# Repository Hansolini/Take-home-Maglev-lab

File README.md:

# Take-home Maglev lab \:magnet\:

<table align="center">
  <tr>
    <td align="center">
      <br>
      1) Current version of the hardware.
    </td>
    <td align="center">
      <br>
      2) Overview of the current PCB.
    </td>
    <td align="center">
      <br>
      2) Magnetic structure of the system.
    </td>
  </tr>
</table>

The "Take-home Maglev lab" is a small lab in development at the Norwegian University of Science and Technology (NTNU), University of Padova, Italy, and University in Stavanger, Norway. The setup is tailored to help students learn control and related fields, and is intended as a kit that students can bring home and assemble independently, with additional lab assignments for teaching anything from fundamental to advanced concepts within control engineering.

If you want to see how the platform looks like and how effective it is to achieve levitation (actually with a PD controller in this case), see [this](https://youtube.com/shorts/XnbO15yq0vE) and [this](https://youtube.com/shorts/F0SiuVEP2tM) videos.

As for this repository, it contains a
- **[MATLAB simulator](./simulation),** implementing several models with examples. See [main.mlx](./simulation/main.mlx) for a guide on how to use it.
- **[Design files & software](./physical_system),** and thus PCB files, test code, with examples for how to use the physical system.
- **[Student contributions](./student_contributions),** i.e., theses and project reports from the students that have contributed to the project.

The following is a table about such student reports, summarizing also the hardware development history.
## Project reports \:books\:
### 2022
 1. [M. Brønstad, J. O. Deila, J. Dyerskog, and M. Langklopp, "Magnetic levitation system: Design, prototyping and testing of a digital PID-controller", B.S. thesis, ITK, NTNU, Trondheim, 2022.](./student_contributions/literature/2022_NTNU_bachelor_thesis_MJJM.pdf)
 2. [A. Morselli, "Re-design of a magnetic levitation platform: from an early prototype to a working system", B.S. thesis, DDD, UNIPD, Padova, 2022.](./student_contributions/literature/2022_UNIPD_bachelor_thesis_alberto_morselli.pdf)
 3. [A. Nicetto, "State Space Observers and Controllers for a Take-Home Magnetic Levitation System", B.S. thesis, DDD, UNIPD, Padova, 2022.](./student_contributions/literature/2022_UNIPD_bachelor_thesis_andrea_nicetto.pdf)
 4. [F. D. Marchi, "Modeling and Control of a Magnetic Levitation System", B.S. thesis, DDD, UNIPD, Padova, 2022.](./student_contributions/literature/2022_UNIPD_bachelor_thesis_francesco_de_marchi.pdf)
### 2023
1. [H. A. Engmark, K. T. Hoang, "Modeling and Control of a Magnetic Levitation Platform.", presented at the 22nd IFAC World Congress, Yokohama, 2023 pp. 7276-7281. ](./media/literature/maglev_model_description.pdf)
2. [A. Lincetto, "Towards a Pythonic framework for control and analysis of magnetic levitation systems", B.S. thesis, DDD, UNIPD, Padova, 2023.](./student_contributions/literature/2023_UNIPD_bachelor_thesis_alessandro_lincetto.pdf)
3. [G. Piccolin, "considerations on the software and hardware requirements for the implementation of take-home Maglev control labs", B.S. thesis, DDD, UNIPD, Padova, 2023.](./student_contributions/literature/2023_UNIPD_bachelor_thesis_giulio_piccolin.pdf)
4. [S. Graffer, "State estimation of a Maglev system with the Luenberger observer", Project thesis, ITK, NTNU, Trondheim, 2023.](./student_contributions/literature/2023_NTNU_project_thesis_sverre_graffer.pdf)
5. [P. I. D. K. Fosmo, "Control of a magnetic levitation system using feedback linearization", Project thesis, ITK, NTNU, Trondheim, 2023.](./student_contributions/literature/2023_NTNU_project_thesis_pål_fosmo.pdf)
6. [S. A. Senkaya, "A take home portable MagLev lab for learning electronics and control", Project thesis, ITK, NTNU, Trondheim, 2023.](./student_contributions/literature/2023_NTNU_project_thesis_sacit_ali_senkaya.pdf)
### 2024
1. [P. I. D. K. Fosmo, S. A. Senkaya, S. Graffer, H. A. Engmark, D. Varagnolo, "Maggy: Hands-on control learning with a maglev system", M.S. thesis, ITK, NTNU, Trondheim, 2024.](https://ntnuopen.ntnu.no/ntnu-xmlui/handle/11250/3153592)
2. [P. I. D. K. Fosmo, H. A. Engmark, D. Varagnolo, "Maglev Systems for Control Education", Maglev24, Malmö, 2024.](https://bth.diva-portal.org/smash/get/diva2:1918096/FULLTEXT01.pdf)
3. [A. Dal Bello, "Tracking Visual Markers For Maglev Platforms", B.S. thesis, DSMN, UNIVE, Venezia, 2024.](./student_contributions/literature/2024_UNIVE_bachelor_thesis_alessandra_dal_bello.pdf)
4. [G. D'Auria, "Computer based state observers for magnet systems", B.S. thesis, DEI, UNIPD, Padova, 2024.](./student_contributions/literature/2024_UNIPD_bachelor_thesis_giuseppe_d'auria.pdf)
### 2025
1. [Ø. Damsgaard, "Moving horizon state estimation for predictive control of magnetic levitation systems", M.S. thesis, ITK, NTNU, Trondheim, 2025](./student_contributions/literature/2025_MSc_thesis_-_Ørnulf_Damsgaard_-_Moving_horizon_state_estimation_for_predictive_control_of_magnetic_levitation_systems.pdf.pdf)
2. [M. Mjelde, "Robust Model Predictive Control for a Magnetic Levitation System", M.S. thesis, ITK, NTNU, Trondheim, 2025](./student_contributions/literature/2025_MSc_thesis_-_Mikael_Mjelde_-_Robust_Model_Predictive_Control_for_a_Maglev.pdf)
3. [L. Ongaro, "Adapting a maglev system for the ball and beam control", B.S. thesis, University of Padova, 2025](./student_contributions/literature/2025_BSc_thesis_Ongaro_Leonardo_Adapting_a_maglev_system_for_the_ball_and_beam_control.pdf)
4. [M. Palamin, "Comunicazione tra un sistema maglev e dispositivi esterni: implementazione e implicazioni per la didattica sulla Teoria del Controllo", B.S. thesis, University of Padova, 2025](./student_contributions/literature/2025_BSc_thesis_Palamin_Manuel_Comunicazione_tra_un_sistema_maglev_e_dispositivi_esterni.pdf)
5. [T. Chinello, "Bode and Nyquist plots for the analysis and control of a magnetic levitation system", B.S. thesis, University of Padova, 2025](./student_contributions/literature/2025_BSc_thesis_Chinello_Tommaso_Bode_and_Nyquist_plots_for_the_analysis_and_control_of_a_magnetic_levitation_system.pdf)
6. [T. A. Jonsson, "Implementation of a Moving Horizon Estimator Using the Acados Framework", M.S. project, ITK, NTNU, Trondheim, 2025](./student_contributions/literature/2025_Prosjektoppgave_-_Thomas_Aleksander_Jonsson_-_MHE_for_Maggy.pdf)
7. [E. Bruaset, "Acados-based Implementation of Nonlinear MPC for Magnetic Levitation", M.S. project, ITK, NTNU, Trondheim, 2025](./student_contributions/literature/2025_Prosjektoppgave_-_Eivind_Bruaset_-_Acados_for_Maggy.pdf)
8. [L. Edvardsen, "Reinforcement Learning for MagLev Control", M.S. project, ITK, NTNU, Trondheim, 2025](./student_contributions/literature/2025_Prosjektoppgave_-_Linus_Edvardsen_-_RL_for_Maggy.pdf)
9. [M. Jullum Faanes, "CasADi-based Implementation of Nonlinear MPC for Magnetic Levitation", M.S. project, ITK, NTNU, Trondheim, 2025](./student_contributions/literature/2025_Prosjektoppgave_-_Marius_Jullum_Faanes_-_SMPC_for_Maggy.pdf)

## Development history \:rocket\:
| **Version** | **Developer**                                                  | **Goal**                                                      | **Development period** |      **Status**      | **Result**                  |
| ----------- | -------------------------------------------------------------- | ------------------------------------------------------------- | ---------------------- | :------------------: | --------------------------- |
| V1.0        | M. Brønstad <br> J. O. Deila <br> J. Dyrskog <br> M. Langklopp | Levitaion                                                     | Spring 2022            | \:white_check_mark\: | Stable levitation ~ 2 min   |
| V2.0        | M. Brønstad <br> J. O. Deila <br> J. Dyrskog                   | Smaller form factor, more robust                              | Summer 2022            | \:white_check_mark\: | Stable levitation >> 2 min  |
| V2.5        | JH Technical AS                                                | Fix minor bugs, improve heating and components                | Spring 2024            | \:white_check_mark\: | Stable levitation >> 2 min  |
| V2.6        | A. Morselli                                                    | Fix faulty wiring, changing sensors                           | Spring 2024            | \:white_check_mark\: | Stable levitation >> 30 min |
| V2.7        | A. Morselli                                                    | Modular design and testbench for V3.0                         | Spring 2024            | \:white_check_mark\: | Decisions on design         |
| V3.0        | A. Morselli                                                    | Modular redesign for first 'Take-home lab'                    | Summer 2024            | \:white_check_mark\: | Decisions on design         |
| V3.1        | M. Leroux                                                      | Adding USB-C power                                            | Fall 2024              | \:white_check_mark\: | Improved power delivery     |
| V4.0        | M. Leroux                                                      | New form factor and additional sensing for improved stability | Fall 2024              | \:white_check_mark\: | Improved control            |
| V4.1        | R. Antonello                                                   | Rerouting PCB tracks and updating components                  | Spring 2025            | \:white_check_mark\: | Meets IPC standards         |
| V4.2        | K. Blom                                                        | Creating a MISO version of the board                          | Spring 2025            | \:white_check_mark\: | MISO board                  |
| V4.3        | A. Morselli                                                    | Improving EM compatibility via some rerouting                 | Fall 2025              | \:white_check_mark\: | Improved EM compatibility   |

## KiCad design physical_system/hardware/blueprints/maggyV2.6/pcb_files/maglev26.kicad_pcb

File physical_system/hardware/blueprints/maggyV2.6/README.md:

#### About the protective covers
All the components are placed slightly off-center with the outline of the PCB. The protective covers are similarly misaligned so that they align well with the PCB.

The cover with the hole is the bottom plate, with the hole giving access to the reset button on the Teensy 4.1.

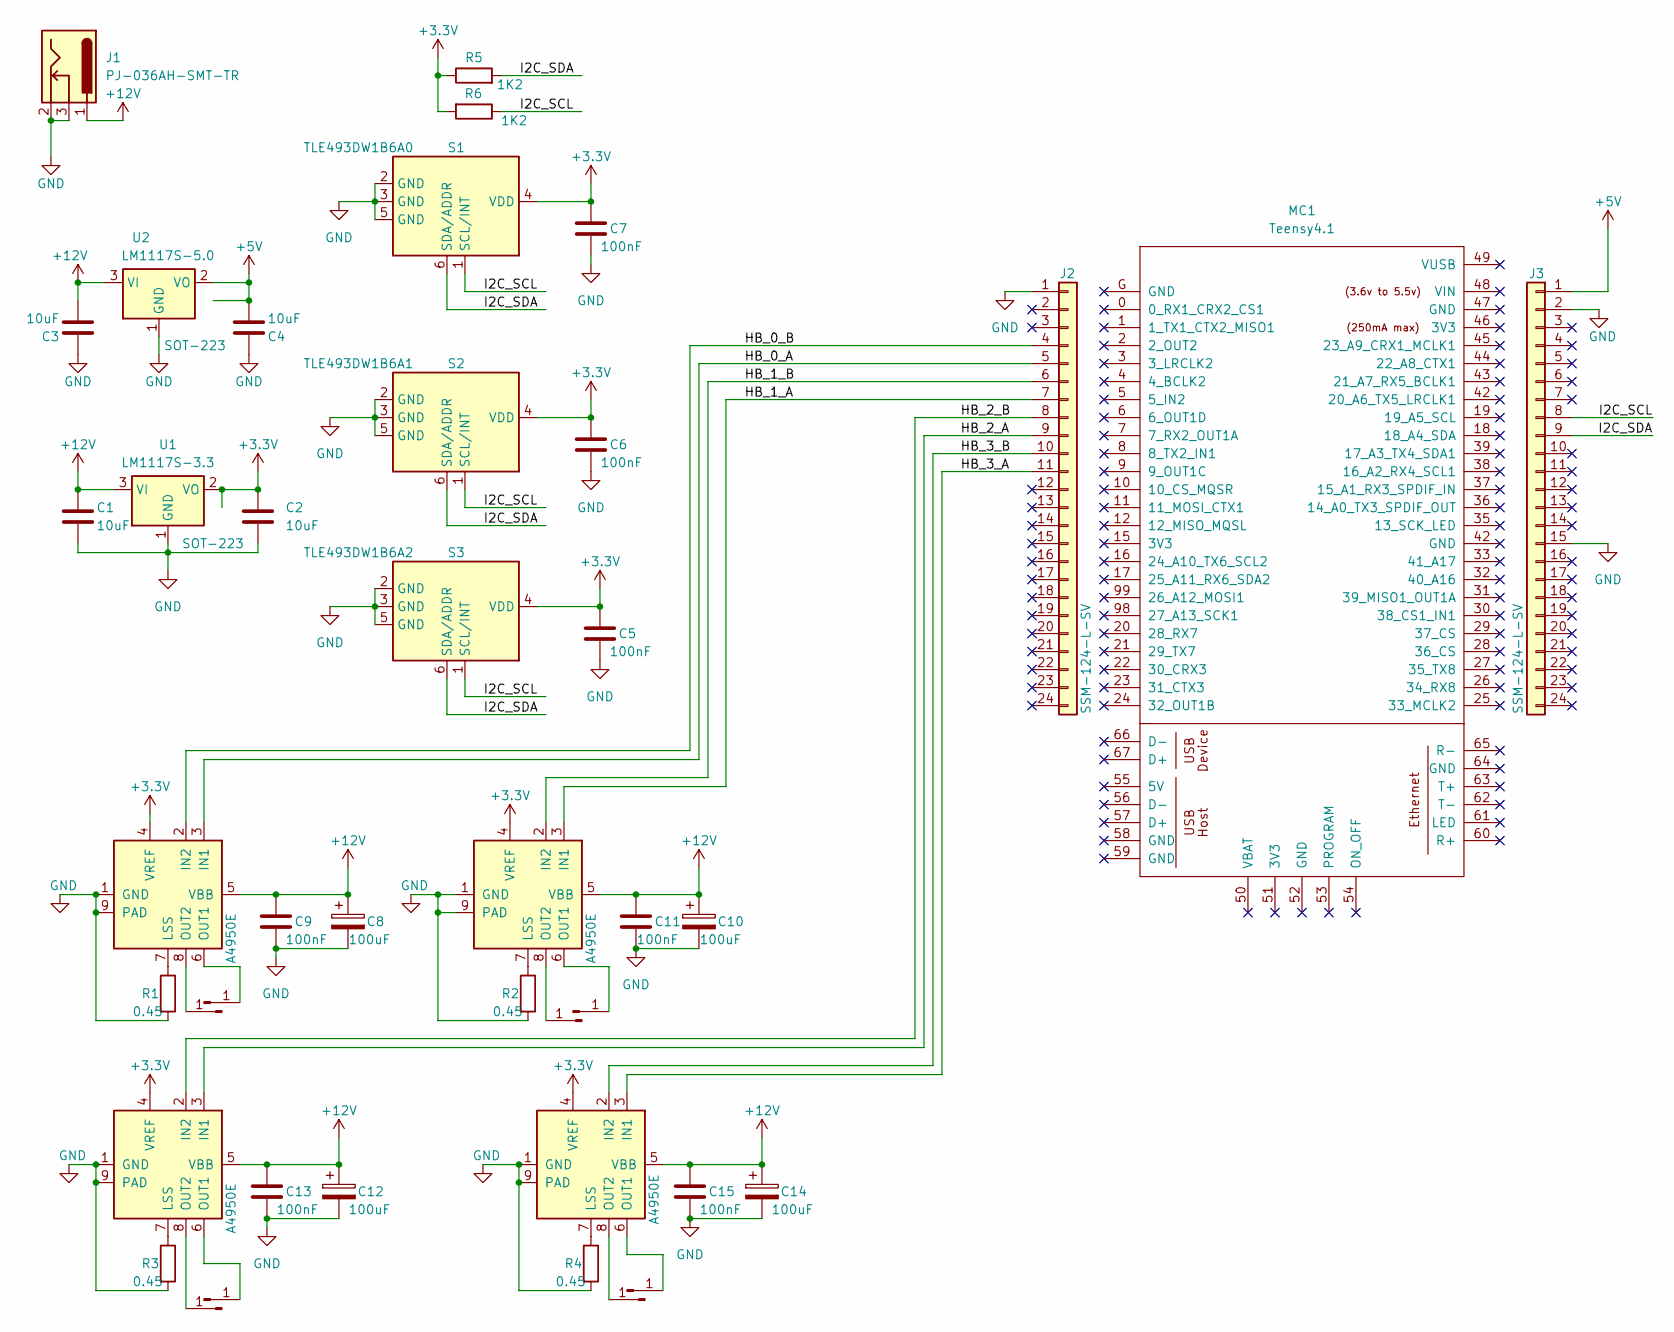
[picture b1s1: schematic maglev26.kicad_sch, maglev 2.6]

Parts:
1_1, 1_2, 2_1, 2_2, 3_1, 3_2, 4_1, 4_2: solenoid; TestPoint_Pad_1.5x1.5mm
C1, C2, C3, C4: 10uF; C_0805_2012Metric
C5, C6, C7, C9, C11, C13, C15: 100nF; C_0603_1608Metric
C8, C10, C12, C14: 100uF; CP_Elec_6.3x7.7
J1: PJ-036AH-SMT-TR; BarrelJack_CUI_PJ-036AH-SMT_Horizontal
J2, J3: SSM-124-L-SV; PinSocket_1x24_P2.54mm_Vertical_SMD_Pin1Left
M1, M2, M3, M4: A4950E; SOIC-8-1EP_3.9x4.9mm_P1.27mm_EP2.41x3.3mm
MC1: Teensy4.1; teensy 4.1
R1, R2, R3, R4: 0.45; R_1206_3216Metric_Pad1.30x1.75mm_HandSolder
R5, R6: 1K2; R_0805_2012Metric
S1: TLE493DW1B6A0; SOT-23-6
S2: TLE493DW1B6A1; SOT-23-6
S3: TLE493DW1B6A2; SOT-23-6
U1: LM1117S-3.3; SOT-223-3_TabPin2
U2: LM1117S-5.0; SOT-223-3_TabPin2

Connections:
+3.3V: C2.1, C5.2, C6.2, C7.2, M1.4 (VREF), M2.4 (VREF), M3.4 (VREF), M4.4 (VREF), R5.1, R6.2, S1.4 (VDD), S2.4 (VDD), S3.4 (VDD), U1.2 (VO); also elsewhere on the board
+5V: C4.2, J3.1, U2.2 (VO); also elsewhere on the board
+12V: C1.1, C3.2, C8.1, C9.1, C10.1, C11.1, C12.1, C13.1, C14.1, C15.1, J1.1, M1.5 (VBB), M2.5 (VBB), M3.5 (VBB), M4.5 (VBB), U1.3 (VI), U2.3 (VI); also elsewhere on the board
/HB_0_A: J2.5, M1.3 (IN1)
/HB_0_B: J2.4, M1.2 (IN2)
/HB_1_A: J2.7, M2.3 (IN1)
/HB_1_B: J2.6, M2.2 (IN2)
/HB_2_A: J2.9, M3.3 (IN1)
/HB_2_B: J2.8, M3.2 (IN2)
/HB_3_A: J2.11, M4.3 (IN1)
/HB_3_B: J2.10, M4.2 (IN2)
/I2C_SCL: J3.8, R6.1, S1.1 (SCL/INT), S2.1 (SCL/INT), S3.1 (SCL/INT)
/I2C_SDA: J3.9, R5.2, S1.6 (SDA/ADDR), S2.6 (SDA/ADDR), S3.6 (SDA/ADDR)
GND: C1.2, C2.2, C3.1, C4.1, C5.1, C6.1, C7.1, C8.2, C9.2, C10.2, C11.2, C12.2, C13.2, C14.2, C15.2, J1.2, J1.3, J2.1, J3.2, J3.15, M1.1 (GND), M1.9 (PAD), M2.1 (GND), M2.9 (PAD), M3.1 (GND), M3.9 (PAD), M4.1 (GND), M4.9 (PAD), R1.2, R2.2, R3.2, R4.2, S1.2 (GND), S1.3 (GND), S1.5 (GND), S2.2 (GND), S2.3 (GND), S2.5 (GND), S3.2 (GND), S3.3 (GND), S3.5 (GND), U1.1 (GND), U2.1 (GND); also elsewhere on the board
unnamed: 1_1.1, M1.6 (OUT1)
unnamed: 1_2.1, M1.8 (OUT2)
unnamed: 2_1.1, M2.6 (OUT1)
unnamed: 2_2.1, M2.8 (OUT2)
unnamed: 3_1.1, M3.6 (OUT1)
unnamed: 3_2.1, M3.8 (OUT2)
unnamed: 4_1.1, M4.6 (OUT1)
unnamed: 4_2.1, M4.8 (OUT2)
unnamed: M1.7 (LSS), R1.1
unnamed: M2.7 (LSS), R2.1
unnamed: M3.7 (LSS), R3.1
unnamed: M4.7 (LSS), R4.1

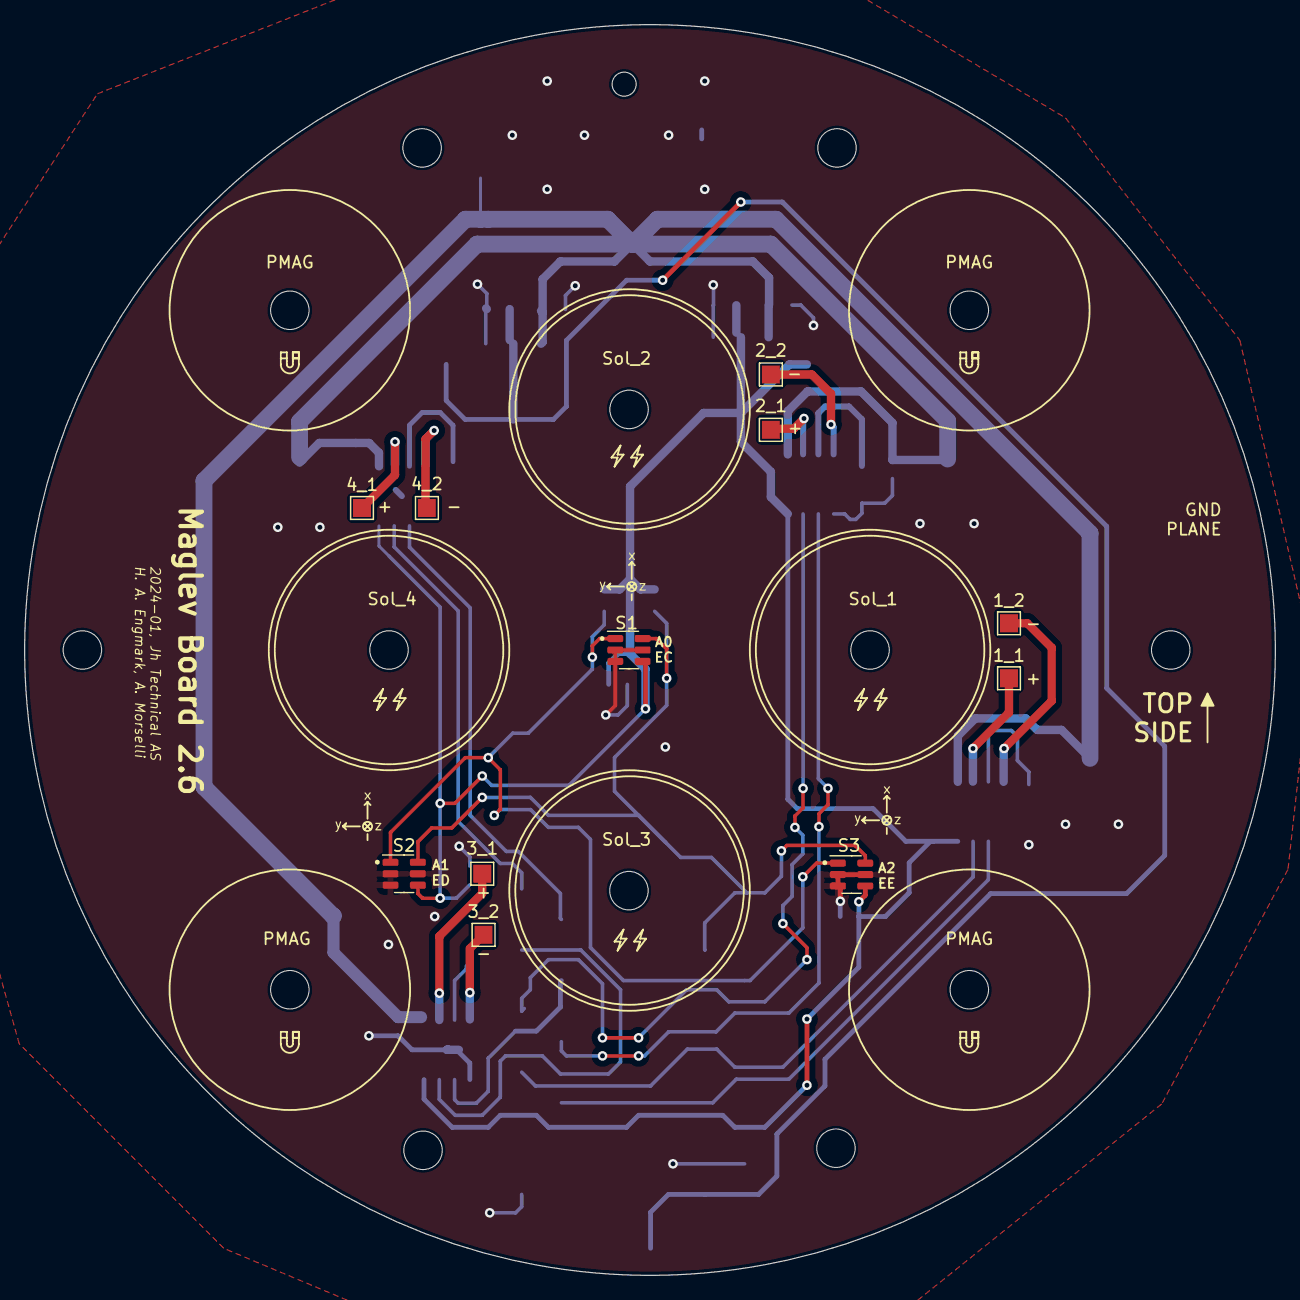
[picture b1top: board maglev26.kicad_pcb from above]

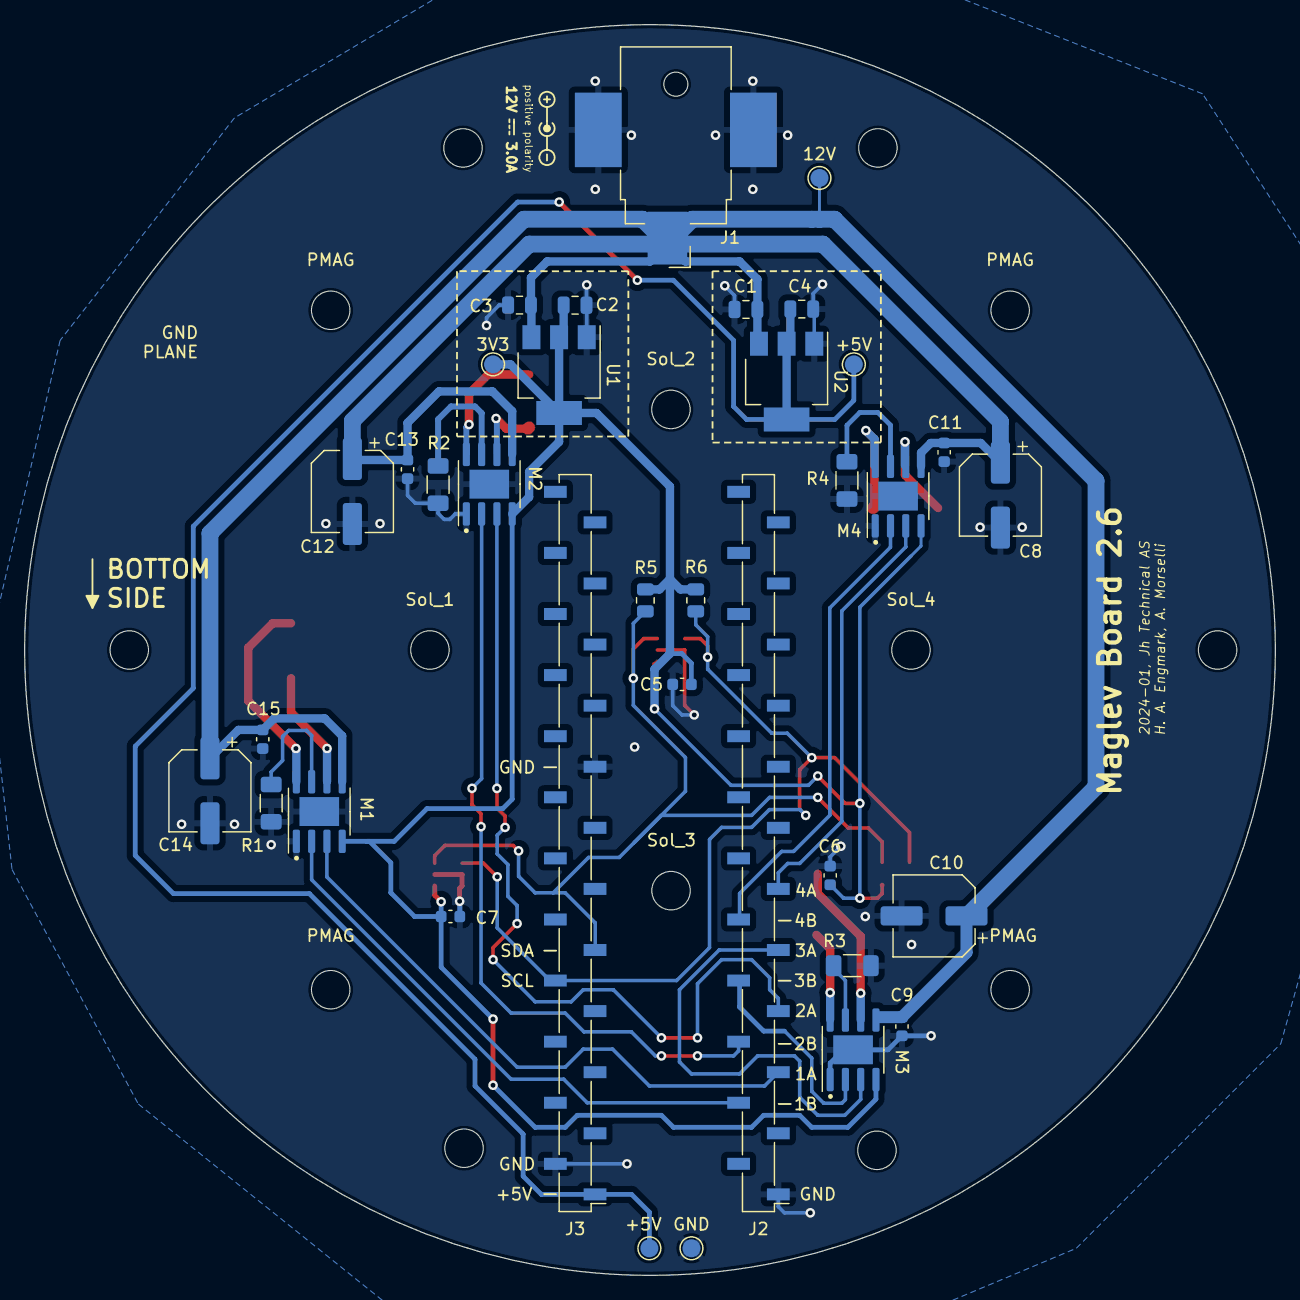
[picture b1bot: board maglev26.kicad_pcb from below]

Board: 2 copper layers, 104.0 x 104.0 mm, 59 parts (48 on the bottom side), 26 nets.

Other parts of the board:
3V3, 12V: TestPoint_Pad_D1.5mm
+5V, +5V#2: TestPoint_Pad_D1.5mm
GND: TestPoint_Pad_D1.5mm
PMAG: MountingHole_3.2mm_M3
PMAG#2, PMAG#3, PMAG#4, PMAG#5, PMAG#6: MountingHole_3.2mm_M3
REF2, REF3, REF4: MountingHole_3.2mm_M3
Sol_1, Sol_2, Sol_3, Sol_4: MountingHole_3.2mm_M3

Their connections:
+3.3V: 3V3.1; also elsewhere on the board
+5V: +5V.1, +5V#2.1; also elsewhere on the board
+12V: 12V.1; also elsewhere on the board
GND: GND.1; also elsewhere on the board

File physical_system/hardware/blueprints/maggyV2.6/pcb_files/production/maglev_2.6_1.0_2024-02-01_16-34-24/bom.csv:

Designator,Footprint,Quantity,Value,LCSC Part #
"C1, C2, C3, C4",0805,4,10uF,
"C10, C12, C14, C8",CP_Elec_6.3x7.7,4,100uF,
"C11, C13, C15, C5, C6, C7, C9",0603,7,100nF,
J1,BarrelJack_CUI_PJ-036AH-SMT_Horizontal,1,PJ-036AH-SMT-TR,
"J2, J3",PinSocket_1x24_P2.54mm_Vertical_SMD_Pin1Left,2,SSM-124-L-SV,
"M1, M2, M3, M4",SOIC-8-1EP_3.9x4.9mm_P1.27mm_EP2.41x3.3mm,4,A4950E,
"R1, R2, R3, R4",1206,4,0.45,
"R5, R6",0805,2,1K2,
S1,SOT-23-6,1,TLE493DW1B6A0,
S2,SOT-23-6,1,TLE493DW1B6A1,
S3,SOT-23-6,1,TLE493DW1B6A2,
U1,SOT-223-3_TabPin2,1,LM1117S-3.3,
U2,SOT-223-3_TabPin2,1,LM1117S-5.0,

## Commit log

2024-01-12 Initial commit
    Initial folder structure and functioning simulator with example file.
2024-01-12 Added an Arduino script and libraries
2024-01-16 Some restructuring of the file structure
2024-01-17 Moving more files around and adding code descriptions
2024-01-17 Removed .asv files
2024-01-17 Added literature and updated readme
2024-01-17 Update README with literature
2024-01-19 Adding some media
2024-01-19 Adding images to README
2024-01-19 Adding PCB blueprints
2024-01-19 Fixing figures in README
2024-01-24 Added student literature
2024-02-01 Updating test code
2024-02-05 First version of the observability test that runs
2024-02-07 Added scaling on states and measurements as described in the paper. The correct system to test was also added. It now produces a result that at least looks meaningful.
2024-02-20 Adding blueprints
2024-02-21 Separated the script in two parts. One is a function for calculating the lui and lecn in a single point. (Most of the content from the original script was put into this one.) The second script is use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
2024-02-21 The description in the last commit is for this one. Forgot to add all the changes.
2024-02-22 Added time vector in the trapz integration. Fixed a bug where the scaling factors for distance and rotations where switced around. Fixed a bug where only the first three out of nine measurements wher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
2024-02-22 Added wait bar that updates whenever the calculation at one point is done. Moved the variable states_to_include from obs_check.m to obs_plot.m
2024-02-22 Added a timestamps matrix witch records a timestamp of when the calculation of the corresponding element in lui an lecn was finished.
2024-02-22 Added additional update messages and saving of mat files
2024-02-22 Fixed syntax error
2024-02-23 Data from observability check
2024-02-25 Updated magnet flipping code
    Successful flip simulation and gif
2024-02-27 Moved results and code for plotting to a new subfolder to avoid accidentally overwriting the results
2024-02-27 Removed hardcoding of number of measurements.
2024-02-27 obs_check.m now returns the simulations results such that obs_plot.m can save them.
2024-02-29 Most of the content of obs_check.m has now been moved into three new functions. obs_check.m now only calls the three new functions. A new section has been added to calc_obs_grid.m which can work on p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
2024-02-29 New data for single sensor experiment
2024-03-28 Added analysis for controllability and observability of linearized model
2024-04-09 Bugfix: Sensor measurements
    All other sensors besides the one in the origin did not measure the field of the levitating magnet correctly.
2024-04-10 Implemented bugfix from Hans. Included new .m file that calculates observability versus sensor placement. Prepared new run of calc_obs_grid.m Changed epsilon to 1e-3.
2024-04-11 Made obsv_vs_sensorpos.m ready for test
2024-04-12 Fixed faulty way of calculating the noise standard deviation. Made obsv_vs_sensorpos.m ready to run.
2024-04-16 Prepared obsv_vs_sensorpos.m for new run.
2024-04-24 Prepared calc_obs_grid.m for new run.
2024-04-29 Prepared calc_obs_grid.m for new run. Let alpha and beta vary.
2024-05-13 Create V2x_PD_example.ino
    Example of implementation of a PD controller
2024-05-25 Adding some tests for students
2024-05-25 New area for calculating average and added functionality for checking observability against rotation of all the sensors around the z-axis
2024-06-13 Added new media
2024-06-13 Added protective cover drawings
2024-06-13 Added observer comparisons examples
2024-09-03 Added PC interface with Matlab example
2024-09-03 Model validation
    Using data from Nikos (youtube)
2024-09-04 Moving some files.
2024-09-07 Bug-fixing typecasting problems
    Premature typecasting in teensy script lead to division by zero in Matlab.
2024-09-14 Fixed issue with motor driver, cleaned up example
    Fixed motor driver issue by changing to "slow decay mode". Cleaned up example code to work with this change (added estimate of solenoid dynamics).
2024-10-11 Adding test to compute direct feedthrough
2025-01-06 Update readme log and new images/illustrations
2025-01-06 Adding two animations.
2025-01-06 Added protective covers V26
2025-01-06 Added design files for V4.0
2025-01-06 Added more production files V2.6
2025-01-06 Added some design files for V2.7
    Only images
2025-01-06 Moved PD example for V2
2025-01-06 Added direct feedthrough copmutatino for V4
2025-01-06 Change name of direct feedthrough test
2025-01-06 Adding some sensor filtering examples
    PD control with different types of filters
2025-01-06 Added V4 example code
2025-01-06 adding model validation
2025-01-06 Reorganized files for SAS thesis
2025-01-06 reorganized files for SAS thesis
    Didn't move the files in the previous commit
2025-01-06 Removing some old files
2025-01-06 Moving magnet flipping example into folder
2025-01-06 Added example teaching material
    Example assignment given in the course TTK4111 at NTNU in the fall of 2024.
2025-01-06 Reorganized files
2025-01-06 Renamed readme file for V40
2025-01-06 fixed images in readme V40
2025-01-08 Renamed folder
2025-01-21 Added results from Giuseppe
2025-01-23 Added contribution from Alessandra
2025-01-23 Updated references with correct departments
2025-01-23 Updated file link in references
2025-01-23 Corrected links in list of contributions
2025-02-03 Create README.md for components
2025-02-06 Fixed issues with TLE implementation
    Sensor has to be initialized before the clock is set
2025-02-07 Fixed example for V4 with TLV sensors
2025-02-07 Added blueprints for V4.1
2025-02-15 Adding questionnaires for trial implementation of lab in course
2025-02-17 Added missing system dynamics functions to TTK4111 example
2025-02-23 Added folder "physical_system/software/V4x_python_interface" containing files of the python interface: work in progress
2025-02-26 Updated maggy.py and added a demo example (demo_example.py) for testing the maggy module
2025-02-28 Added 2D model based on infinitesimal dipoles
2025-03-01 Added automatic feedthrough calibration
2025-03-02 Added simulink example of simple 2D model
2025-03-07 Various updates to V4x PD Example
    Added:
    - Filtering on input
    - Anti sensor lock-up
    - Fixed reset on power-up
    - Better tuning
2025-03-21 V4x_python_interface_COBS
    New version of the maggy.py interface and PD controller in Python
2025-03-21 V4x_python-interface_COBS
    created a new folder "V4x_python-interface_COBS"
2025-03-21 Moved files into correct folder "V4x_python-interface_COBS"
2025-03-22 Added 3D dipole model of maggy
2025-03-23 Correction to finding equilibrium
2025-03-23 Added extra damping effects in z direction
2025-03-23 Added a reduced order (10 states) dipole model
2025-03-28 Added README.md arduino setup guide
2025-03-28 Corrected name of README
2025-04-02 python interface last version - only control loop on python
2025-04-04 Updated V4x example for robustness
    Added reading from multiple sensors, reorganized functions and files, added more robust sensor freeze recovery, added user friendly description at the head of the main file
2025-04-04 Freeze fix (?) - re-enabling multiplexer when reading data
2025-09-07 Many changes!
2025-09-07 More student contributions
2025-09-07 Added code for Ørnulf master thesis
2025-09-28 Fixed reshaping issue
2026-04-14 Added two images of the physical system 4.0
2026-04-16 Added a few .pdfs of theses that were missing in the repo
